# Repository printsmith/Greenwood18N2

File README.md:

# SP-110 Duo
Custom keyboard featuring a modified Southpaw 1800 layout with 2 nav clusters, LCD display and rotary encoders.

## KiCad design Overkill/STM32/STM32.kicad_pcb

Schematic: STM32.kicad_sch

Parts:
BT1: Battery_Cell; BatteryHolder_Keystone_1060_1x2032
C1, C15: 4.7u; C_0603_1608Metric_Pad1.08x0.95mm_HandSolder
C2, C3, C4, C5, C6, C7, C8, C9, C11, C12, C13, C14, C19, C20, C22, C23: 100n; C_0603_1608Metric_Pad1.08x0.95mm_HandSolder
C16, C17: 1u; C_0603_1608Metric_Pad1.08x0.95mm_HandSolder
C18, C24, C25, C26, C27, C28, C29, C30, C31, C32, C33: 100u; CP_EIA-6032-15_Kemet-U_Pad2.25x2.35mm_HandSolder
C21: 100nF; C_0603_1608Metric_Pad1.08x0.95mm_HandSolder
D1, D2, D3, D4, D5, D6, D7, D8, D9, D10, D11, D12, D13, D14, D15, D16, D17, D18, D19, D20, D21, D22, D23, D24, D25, D26, D27, D28, D29, D30, D31, D32, D33, D34, D35, D36, D37, D38, D39, D40, D41, D42, D43, D44, D45, D46, D47, D48, D49, D50, D51, D52, D53, D54, D55, D56, D57, D58, D59, D60, D61, D62, D63, D64, D65, D66, D67, D68, D69, D70, D71, D72, D73, D74, D75, D76, D77, D78, D79, D80, D81, D82, D83, D84, D85, D86, D87, D88, D89, D90, D91, D92, D93, D94, D95, D96, D97, D98, D99, D100, D101, D102, D103, D104, D105, D106, D107, D108, D109, D110, D111, D112, D113, D114, D115, D116, D117: D; D_SOD-123F
D118: SMF5.0CA; D_SOD-123F
D119, D120: 1N4148; D_SOD-123F
F1: 3.0A 1206 Polyfuse; Fuse_1206_3216Metric_Pad1.42x1.75mm_HandSolder
FB1: 4A/0805; Fuse_0805_2012Metric_Pad1.15x1.40mm_HandSolder
H1, H2, H3, H4, H5, H6, H7, H8, H9, H10: MountingHole; MountingHole_2.2mm_M2_DIN965_Pad
J1: USB_C_Receptacle_USB2.0; HRO-TYPE-C-31-M-12-HandSoldering-NoSBU
JP1: SolderJumper_2_Open; SolderJumper-2_P1.3mm_Open_TrianglePad1.0x1.5mm
LCD1: LCD-ST7789-2in
LED1, LED2, LED3, LED4, LED5, LED6, LED7, LED8, LED9, LED10, LED11, LED12, LED13, LED14, LED15, LED16, LED17, LED18, LED19, LED40, LED41, LED42, LED43, LED44, LED45, LED46, LED47, LED48, LED49, LED50, LED51, LED52, LED53, LED54, LED55, LED56, LED57, LED58, LED59, LED79, LED80, LED81, LED82, LED83, LED84, LED85, LED86, LED87, LED88, LED89, LED90, LED91, LED92, LED93, LED94, LED95, LED96, LED97: MX_SK6803MINI-E; LED_MX_6028R-ROT
LED20, LED21, LED22, LED23, LED24, LED25, LED26, LED27, LED28, LED29, LED30, LED31, LED32, LED33, LED34, LED35, LED36, LED37, LED38, LED39, LED60, LED61, LED62, LED63, LED64, LED65, LED66, LED67, LED68, LED69, LED70, LED71, LED72, LED73, LED74, LED75, LED76, LED77, LED78, LED98, LED99, LED100, LED101, LED102, LED103, LED104, LED105, LED106, LED107, LED108, LED109, LED110, LED111: MX_SK6803MINI-E; LED_MX_6028R
MX1, MX2, MX3, MX4, MX5, MX6, MX7, MX8, MX9, MX10, MX11, MX12, MX13, MX14, MX15, MX16, MX17, MX18, MX19, MX20, MX21, MX22, MX23, MX24, MX25, MX26, MX27, MX28, MX29, MX30, MX31, MX32, MX33, MX34, MX35, MX36, MX37, MX39, MX40, MX41, MX42, MX43, MX44, MX46, MX47, MX48, MX49, MX50, MX51, MX52, MX53, MX54, MX55, MX56, MX57, MX59, MX60, MX61, MX62, MX63, MX64, MX66, MX67, MX68, MX69, MX70, MX71, MX72, MX73, MX74, MX75, MX76, MX78, MX79, MX81, MX82, MX83, MX85, MX86, MX87, MX88, MX89, MX90, MX91, MX92, MX93, MX94, MX96, MX97, MX98, MX99, MX109, MX110, MX111: MX_SW_HS; SW_MX_HS_1u
MX38, MX100: MX_SW_HS; SW_MX_HS_2u
MX45, MX58, MX107, MX108: MX_SW_HS; SW_MX_HS_1.5u
MX65, MX95: MX_SW_HS; SW_MX_HS_1.75u
MX77, MX84, MX106: MX_SW_HS; SW_MX_HS_2.25u
MX80: MX_SW_HS; SW_MX_HS_2u_Vertical
MX101, MX102, MX103, MX105: MX_SW_HS; SW_MX_HS_1.25u
MX104: MX_SW_HS; SW_MX_HS_2.75u
Q1, Q2: AO3401A; SOT-23-3
Q3: MMUN2133LT1G; SOT-23-3
Q4, Q6: 2N7002; SOT-23-3
Q7: AO3401A; SOT-23
Q8: MMUN2233LT1G; SOT-23-3
R1: 120; R_0603_1608Metric_Pad0.98x0.95mm_HandSolder
R2, R3, R9, R15, R17, R20, R21, R22, R23, R24, R25: 68k; R_0603_1608Metric_Pad0.98x0.95mm_HandSolder
R4, R5, R6, R7, R8, R10, R11, R12, R13, R14, R16, R18, R19, R26, R27: 9.1k; R_0603_1608Metric_Pad0.98x0.95mm_HandSolder
R28: 9.1k; R_0805_2012Metric
RESET1: DFU; SW_SPST_SKQG_WithStem
SW1: RKJXT1F42001; Mouser Part Number 688-RKJXT1F42001
SW2: RotaryEncoder_Switch; RotaryEncoder_Alps_EC11E-Switch_Vertical_H20mm_Centred
TP1: VBUS; TestPoint
TP2: 5V; TestPoint
TP3: 3V3; TestPoint
TP4: GND; TestPoint
TP5: RST; TestPoint
TP6: SWC; TestPoint
TP7: SWD; TestPoint
U1: AZC199-04S; SOT-23-6
U2: W25Q32JVSSIQ; SOIC-8_5.23x5.23mm_P1.27mm
U3: LMV321; SOT-23-5
U4: MB85RS64; SOIC-8_3.9x4.9mm_P1.27mm
U5: AZ1117H-3.3TRE1; SOT-23-3
U6: STM32G474RETx; LQFP-64_10x10mm_P0.5mm
U7, U8: TPS2553DBVR-1; SOT-23-6_Handsoldering

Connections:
+3V3: C1.1, C2.1, C3.1, C4.1, C5.1, C6.1, C7.1, C11.1, C12.1, C17.2, JP1.1 (A), Q3.2 (E), R7.2, R10.2, R12.2, R14.2, TP3.1, U2.8 (VCC), U4.3 (~W), U4.7 (~HOLD), U4.8 (VCC), U5.2 (VO), U6.16 (VDD), U6.28 (VREF+), U6.29 (VDDA), U6.32 (VDD), U6.48 (VDD), U6.64 (VDD)
+5V: TP2.1
/VBUS_BLOCKED: Q1.2 (S), Q2.3 (D), R9.1, U1.5 (VBUS), U3.3 (-)
/VBUS_FERRITE: F1.2, FB1.1
/VBUS_FUSED: D118.1 (A1), F1.1, Q1.3 (D)
BOARD_NFAULT: R4.2, U6.30 (PB10), U7.4 (~FAULT)
BOOT0: C13.2, C14.2, R1.2, R2.2, U6.61 (PB8)
BOOT0_CHRG: D119.2 (A), Q3.1 (B), U6.60 (PB7)
CC1: J1.B5 (CC2), U1.3 (I/O4), U6.43 (PA9), U6.59 (PB6)
CC2: J1.A5 (CC1), U1.1 (I/O1), U6.44 (PA10), U6.57 (PB4)
COL3: MX6.1, MX7.1, MX26.1, MX27.1, MX46.1, MX47.1, MX66.1, MX67.1, MX85.1, MX102.1, MX103.1, U6.41 (PC9)
COL4: MX8.1, MX9.1, MX28.1, MX29.1, MX48.1, MX49.1, MX68.1, MX69.1, MX86.1, MX87.1, MX104.1, U6.40 (PC8)
COL5: MX10.1, MX11.1, MX30.1, MX31.1, MX50.1, MX51.1, MX70.1, MX71.1, MX88.1, MX89.1, MX105.1, U6.39 (PC7)
COL6: MX12.1, MX13.1, MX32.1, MX33.1, MX52.1, MX53.1, MX72.1, MX73.1, MX90.1, MX91.1, MX106.1, U6.38 (PC6)
COL7: MX14.1, MX15.1, MX34.1, MX35.1, MX54.1, MX55.1, MX74.1, MX75.1, MX92.1, MX93.1, MX107.1, U6.37 (PB15)
COL8: MX16.1, MX17.1, MX36.1, MX37.1, MX56.1, MX57.1, MX76.1, MX94.1, MX95.1, MX108.1, MX109.1, U6.36 (PB14)
COL9: MX18.1, MX19.1, MX38.1, MX39.1, MX58.1, MX59.1, MX77.1, MX78.1, MX96.1, MX97.1, MX110.1, MX111.1, U6.35 (PB13)
COL10: SW1.7 (COM)
CURR_1500mA_OK: Q4.1 (G), R26.1, U6.25 (PB1)
CURR_3000mA_OK: Q6.1 (G), R27.1, U6.24 (PB0)
CURR_LIM: R20.1, R23.1, R24.1, R25.1, U8.5 (ILIM)
D+: J1.A6 (D+), J1.B6 (D+), U1.6 (I/O2), U6.46 (PA12)
D-: J1.A7 (D-), J1.B7 (D-), U1.4 (I/O3), U6.45 (PA11)
EEP_CS: U4.1 (~S), U6.58 (PB5)
ENC1: D112.2 (A), SW2.S2
ENC1_A: C19.2, R8.1
ENC1_B: C20.2, R11.2
ENC2_A: C21.2, R13.1, U6.21 (PA7)
ENC2_B: C22.2, R16.2, U6.22 (PC4)
FLASH_CS: U2.1 (~CS), U6.42 (PA8)
LCD_BL_PWM: LCD1.8, U6.2 (PC13)
LCD_CS: LCD1.7, U6.62 (PB9)
LCD_DC: LCD1.6, U6.56 (PB3)
LCD_RST: LCD1.5, U6.55 (PD2)
LED_EN: R19.1, U6.33 (PB11), U8.3 (EN)
LED_MTRX_IN: LED4.3 (DIN), R28.2, U6.23 (PC5)
LED_NFAULT: R18.2, U6.26 (PB2), U8.4 (~FAULT)
LED_PWR: C24.1, C25.1, C26.1, C27.1, C28.1, C29.1, C30.1, C31.1, C32.1, C33.1, LED1.1 (VDD), LED2.1 (VDD), LED3.1 (VDD), LED4.1 (VDD), LED5.1 (VDD), LED6.1 (VDD), LED7.1 (VDD), LED8.1 (VDD), LED9.1 (VDD), LED10.1 (VDD), LED11.1 (VDD), LED12.1 (VDD), LED13.1 (VDD), LED14.1 (VDD), LED15.1 (VDD), LED16.1 (VDD), LED17.1 (VDD), LED18.1 (VDD), LED19.1 (VDD), LED20.1 (VDD), LED21.1 (VDD), LED22.1 (VDD), LED23.1 (VDD), LED24.1 (VDD), LED25.1 (VDD), LED26.1 (VDD), LED27.1 (VDD), LED28.1 (VDD), LED29.1 (VDD), LED30.1 (VDD), LED31.1 (VDD), LED32.1 (VDD), LED33.1 (VDD), LED34.1 (VDD), LED35.1 (VDD), LED36.1 (VDD), LED37.1 (VDD), LED38.1 (VDD), LED39.1 (VDD), LED40.1 (VDD), LED41.1 (VDD), LED42.1 (VDD), LED43.1 (VDD), LED44.1 (VDD), LED45.1 (VDD), LED46.1 (VDD), LED47.1 (VDD), LED48.1 (VDD), LED49.1 (VDD), LED50.1 (VDD), LED51.1 (VDD), LED52.1 (VDD), LED53.1 (VDD), LED54.1 (VDD), LED55.1 (VDD), LED56.1 (VDD), LED57.1 (VDD), LED58.1 (VDD), LED59.1 (VDD), LED60.1 (VDD), LED61.1 (VDD), LED62.1 (VDD), LED63.1 (VDD), LED64.1 (VDD), LED65.1 (VDD), LED66.1 (VDD), LED67.1 (VDD), LED68.1 (VDD), LED69.1 (VDD), LED70.1 (VDD), LED71.1 (VDD), LED72.1 (VDD), LED73.1 (VDD), LED74.1 (VDD), LED75.1 (VDD), LED76.1 (VDD), LED77.1 (VDD), LED78.1 (VDD), LED79.1 (VDD), LED80.1 (VDD), LED81.1 (VDD), LED82.1 (VDD), LED83.1 (VDD), LED84.1 (VDD), LED85.1 (VDD), LED86.1 (VDD), LED87.1 (VDD), LED88.1 (VDD), LED89.1 (VDD), LED90.1 (VDD), LED91.1 (VDD), LED92.1 (VDD), LED93.1 (VDD), LED94.1 (VDD), LED95.1 (VDD), LED96.1 (VDD), LED97.1 (VDD), LED98.1 (VDD), LED99.1 (VDD), LED100.1 (VDD), LED101.1 (VDD), LED102.1 (VDD), LED103.1 (VDD), LED104.1 (VDD), LED105.1 (VDD), LED106.1 (VDD), LED107.1 (VDD), LED108.1 (VDD), LED109.1 (VDD), LED110.1 (VDD), LED111.1 (VDD), R28.1, U8.6 (OUT)
MISO: U2.2 (DO(IO1)), U4.2 (Q), U6.53 (PC11)
MOSI: LCD1.4, U2.5 (DI(IO0)), U4.5 (D), U6.54 (PC12)
NRST: C9.2, D120.2 (A), U6.7 (PG10)
unnamed: D1.2 (A), MX1.2
unnamed: D2.1 (K), MX2.2
unnamed: D3.2 (A), MX3.2
unnamed: D4.1 (K), MX4.2
unnamed: D5.2 (A), MX5.2
unnamed: D6.1 (K), MX6.2
unnamed: D7.2 (A), MX7.2
unnamed: D8.1 (K), MX8.2
unnamed: D9.2 (A), MX9.2
unnamed: D10.1 (K), MX10.2
unnamed: D11.2 (A), MX11.2
unnamed: D12.1 (K), MX12.2
unnamed: D13.2 (A), MX13.2
unnamed: D14.1 (K), MX14.2
unnamed: D15.2 (A), MX15.2
unnamed: D16.1 (K), MX16.2
unnamed: D17.2 (A), MX17.2
unnamed: D18.1 (K), MX18.2
unnamed: D19.2 (A), MX19.2
unnamed: D20.1 (K), MX20.2
unnamed: D21.2 (A), MX21.2
unnamed: D22.1 (K), MX22.2
unnamed: D23.2 (A), MX23.2
unnamed: D24.1 (K), MX24.2
unnamed: D25.2 (A), MX25.2
unnamed: D26.1 (K), MX26.2
unnamed: D27.2 (A), MX27.2
unnamed: D28.1 (K), MX28.2
unnamed: D29.2 (A), MX29.2
unnamed: D30.1 (K), MX30.2
unnamed: D31.2 (A), MX31.2
unnamed: D32.1 (K), MX32.2
unnamed: D33.2 (A), MX33.2
unnamed: D34.1 (K), MX34.2
unnamed: D35.2 (A), MX35.2
unnamed: D36.1 (K), MX36.2
unnamed: D37.2 (A), MX37.2
unnamed: D38.1 (K), MX38.2
unnamed: D39.2 (A), MX39.2
unnamed: D40.1 (K), MX40.2
unnamed: D41.2 (A), MX41.2
unnamed: D42.1 (K), MX42.2
unnamed: D43.2 (A), MX43.2
unnamed: D44.1 (K), MX44.2
unnamed: D45.2 (A), MX45.2
unnamed: D46.1 (K), MX46.2
unnamed: D47.2 (A), MX47.2
unnamed: D48.1 (K), MX48.2
unnamed: D49.2 (A), MX49.2
unnamed: D50.1 (K), MX50.2
unnamed: D51.2 (A), MX51.2
unnamed: D52.1 (K), MX52.2
unnamed: D53.2 (A), MX53.2
unnamed: D54.1 (K), MX54.2
unnamed: D55.2 (A), MX55.2
unnamed: D56.1 (K), MX56.2
unnamed: D57.2 (A), MX57.2
unnamed: D58.1 (K), MX58.2
unnamed: D59.2 (A), MX59.2
unnamed: D60.1 (K), MX60.2
unnamed: D61.2 (A), MX61.2
unnamed: D62.1 (K), MX62.2
unnamed: D63.2 (A), MX63.2
unnamed: D64.1 (K), MX64.2
unnamed: D65.2 (A), MX65.2
unnamed: D66.1 (K), MX66.2
unnamed: D67.2 (A), MX67.2
unnamed: D68.1 (K), MX68.2
unnamed: D69.2 (A), MX69.2
unnamed: D70.1 (K), MX70.2
unnamed: D71.2 (A), MX71.2
unnamed: D72.1 (K), MX72.2
unnamed: D73.2 (A), MX73.2
unnamed: D74.1 (K), MX74.2
unnamed: D75.2 (A), MX75.2
unnamed: D76.1 (K), MX76.2
unnamed: D77.1 (K), MX77.2
unnamed: D78.2 (A), MX78.2
unnamed: D79.1 (K), MX79.2
unnamed: D81.1 (K), MX81.2
unnamed: D82.2 (A), MX82.2
unnamed: D83.1 (K), MX83.2
unnamed: D84.2 (A), MX84.2
unnamed: D85.2 (A), MX85.2
unnamed: D86.1 (K), MX86.2
unnamed: D87.2 (A), MX87.2
unnamed: D88.1 (K), MX88.2
unnamed: D89.2 (A), MX89.2
unnamed: D90.1 (K), MX90.2
unnamed: D91.2 (A), MX91.2
unnamed: D92.1 (K), MX92.2
unnamed: D93.2 (A), MX93.2
unnamed: D94.1 (K), MX94.2
unnamed: D95.2 (A), MX95.2
unnamed: D96.1 (K), MX96.2
unnamed: D97.2 (A), MX97.2
unnamed: D98.1 (K), MX98.2
unnamed: D99.1 (K), MX99.2
unnamed: D100.1 (K), MX100.2
unnamed: D101.2 (A), MX101.2
unnamed: D102.1 (K), MX102.2
unnamed: D103.2 (A), MX103.2
unnamed: D104.2 (A), MX104.2
unnamed: D105.2 (A), MX105.2
unnamed: D106.2 (A), MX106.2
unnamed: D107.2 (A), MX107.2
unnamed: D108.1 (K), MX108.2
unnamed: D109.2 (A), MX109.2
unnamed: D110.1 (K), MX110.2
unnamed: D111.2 (A), MX111.2
unnamed: D119.1 (K), D120.1 (K), RESET1.2
unnamed: LED1.3 (DIN), LED2.2 (DOUT)
unnamed: LED1.2 (DOUT), LED20.3 (DIN)
unnamed: LED2.3 (DIN), LED3.2 (DOUT)
unnamed: LED3.3 (DIN), LED4.2 (DOUT)
unnamed: LED5.3 (DIN), LED6.2 (DOUT)
unnamed: LED6.3 (DIN), LED7.2 (DOUT)
unnamed: LED7.3 (DIN), LED8.2 (DOUT)
unnamed: LED8.3 (DIN), LED9.2 (DOUT)
unnamed: LED10.3 (DIN), LED11.2 (DOUT)
unnamed: LED9.3 (DIN), LED10.2 (DOUT)
unnamed: LED11.3 (DIN), LED12.2 (DOUT)
unnamed: LED12.3 (DIN), LED13.2 (DOUT)
unnamed: LED13.3 (DIN), LED14.2 (DOUT)
unnamed: LED14.3 (DIN), LED15.2 (DOUT)
unnamed: LED15.3 (DIN), LED16.2 (DOUT)
unnamed: LED16.3 (DIN), LED17.2 (DOUT)
unnamed: LED17.3 (DIN), LED18.2 (DOUT)
unnamed: LED18.3 (DIN), LED19.2 (DOUT)
unnamed: LED19.3 (DIN), LED39.2 (DOUT)
unnamed: LED20.2 (DOUT), LED21.3 (DIN)
unnamed: LED21.2 (DOUT), LED22.3 (DIN)
unnamed: LED22.2 (DOUT), LED23.3 (DIN)
unnamed: LED23.2 (DOUT), LED24.3 (DIN)
unnamed: LED24.2 (DOUT), LED44.3 (DIN)
unnamed: LED25.3 (DIN), LED45.2 (DOUT)
unnamed: LED25.2 (DOUT), LED26.3 (DIN)
unnamed: LED26.2 (DOUT), LED27.3 (DIN)
unnamed: LED27.2 (DOUT), LED28.3 (DIN)
unnamed: LED28.2 (DOUT), LED29.3 (DIN)
unnamed: LED29.2 (DOUT), LED30.3 (DIN)
unnamed: LED30.2 (DOUT), LED31.3 (DIN)
unnamed: LED31.2 (DOUT), LED32.3 (DIN)
unnamed: LED32.2 (DOUT), LED33.3 (DIN)
unnamed: LED33.2 (DOUT), LED34.3 (DIN)
unnamed: LED34.2 (DOUT), LED35.3 (DIN)
unnamed: LED35.2 (DOUT), LED36.3 (DIN)
unnamed: LED36.2 (DOUT), LED37.3 (DIN)
unnamed: LED37.2 (DOUT), LED38.3 (DIN)
unnamed: LED38.2 (DOUT), LED39.3 (DIN)
unnamed: LED40.3 (DIN), LED41.2 (DOUT)
unnamed: LED40.2 (DOUT), LED60.3 (DIN)
unnamed: LED41.3 (DIN), LED42.2 (DOUT)
unnamed: LED42.3 (DIN), LED43.2 (DOUT)
unnamed: LED43.3 (DIN), LED44.2 (DOUT)
unnamed: LED45.3 (DIN), LED46.2 (DOUT)
unnamed: LED46.3 (DIN), LED47.2 (DOUT)
unnamed: LED47.3 (DIN), LED48.2 (DOUT)
unnamed: LED48.3 (DIN), LED49.2 (DOUT)
unnamed: LED49.3 (DIN), LED50.2 (DOUT)
unnamed: LED50.3 (DIN), LED51.2 (DOUT)
unnamed: LED51.3 (DIN), LED52.2 (DOUT)
unnamed: LED52.3 (DIN), LED53.2 (DOUT)
unnamed: LED53.3 (DIN), LED54.2 (DOUT)
unnamed: LED54.3 (DIN), LED55.2 (DOUT)
unnamed: LED55.3 (DIN), LED56.2 (DOUT)
unnamed: LED56.3 (DIN), LED57.2 (DOUT)
unnamed: LED57.3 (DIN), LED58.2 (DOUT)
unnamed: LED58.3 (DIN), LED59.2 (DOUT)
unnamed: LED59.3 (DIN), LED78.2 (DOUT)
unnamed: LED60.2 (DOUT), LED61.3 (DIN)
unnamed: LED61.2 (DOUT), LED62.3 (DIN)
unnamed: LED62.2 (DOUT), LED63.3 (DIN)
unnamed: LED63.2 (DOUT), LED64.3 (DIN)
unnamed: LED64.2 (DOUT), LED83.3 (DIN)
unnamed: LED65.3 (DIN), LED84.2 (DOUT)
unnamed: LED65.2 (DOUT), LED66.3 (DIN)
unnamed: LED66.2 (DOUT), LED67.3 (DIN)
unnamed: LED67.2 (DOUT), LED68.3 (DIN)
unnamed: LED68.2 (DOUT), LED69.3 (DIN)
unnamed: LED69.2 (DOUT), LED70.3 (DIN)
unnamed: LED70.2 (DOUT), LED71.3 (DIN)
unnamed: LED71.2 (DOUT), LED72.3 (DIN)
unnamed: LED72.2 (DOUT), LED73.3 (DIN)
unnamed: LED73.2 (DOUT), LED74.3 (DIN)
unnamed: LED74.2 (DOUT), LED75.3 (DIN)
unnamed: LED75.2 (DOUT), LED76.3 (DIN)
unnamed: LED76.2 (DOUT), LED77.3 (DIN)
unnamed: LED77.2 (DOUT), LED78.3 (DIN)
unnamed: LED79.3 (DIN), LED80.2 (DOUT)
unnamed: LED79.2 (DOUT), LED98.3 (DIN)
unnamed: LED80.3 (DIN), LED81.2 (DOUT)
unnamed: LED81.3 (DIN), LED82.2 (DOUT)
unnamed: LED82.3 (DIN), LED83.2 (DOUT)
unnamed: LED84.3 (DIN), LED85.2 (DOUT)
unnamed: LED85.3 (DIN), LED86.2 (DOUT)
unnamed: LED86.3 (DIN), LED87.2 (DOUT)
unnamed: LED87.3 (DIN), LED88.2 (DOUT)
unnamed: LED88.3 (DIN), LED89.2 (DOUT)
unnamed: LED89.3 (DIN), LED90.2 (DOUT)
unnamed: LED90.3 (DIN), LED91.2 (DOUT)
unnamed: LED91.3 (DIN), LED92.2 (DOUT)
unnamed: LED92.3 (DIN), LED93.2 (DOUT)
unnamed: LED93.3 (DIN), LED94.2 (DOUT)
unnamed: LED94.3 (DIN), LED95.2 (DOUT)
unnamed: LED95.3 (DIN), LED97.2 (DOUT)
unnamed: LED96.2 (DOUT), LED97.3 (DIN)
unnamed: LED98.2 (DOUT), LED99.3 (DIN)
unnamed: LED99.2 (DOUT), LED100.3 (DIN)
unnamed: LED100.2 (DOUT), LED101.3 (DIN)
unnamed: LED101.2 (DOUT), LED102.3 (DIN)
unnamed: LED102.2 (DOUT), LED103.3 (DIN)
unnamed: LED103.2 (DOUT), LED104.3 (DIN)
unnamed: LED104.2 (DOUT), LED105.3 (DIN)
unnamed: LED105.2 (DOUT), LED106.3 (DIN)
unnamed: LED106.2 (DOUT), LED107.3 (DIN)
unnamed: LED107.2 (DOUT), LED108.3 (DIN)
unnamed: LED108.2 (DOUT), LED109.3 (DIN)
unnamed: LED109.2 (DOUT), LED110.3 (DIN)
unnamed: LED110.2 (DOUT), LED111.3 (DIN)
unnamed: LED96.3 (DIN), LED111.2 (DOUT)
unnamed: Q2.1 (G), U3.4
unnamed: Q3.3 (C), R1.1
unnamed: Q4.3 (D), R23.2
unnamed: Q6.3 (D), R24.2, R25.2
unnamed: R2.1, R3.1
unnamed: R5.2, R6.1
unnamed: R15.2, R17.1
unnamed: R20.2, R21.2
unnamed: R21.1, R22.1
unnamed: R5.1, U7.5 (ILIM)
PLUG_DETECT: R9.2, R15.1, U6.34 (PB12)
RESET: TP5.1
RKJ-A: D116.2 (A), SW1.1 (A)
RKJ-B: D114.2 (A), SW1.4 (B)
RKJ-C: D113.2 (A), SW1.6 (C)
RKJ-D: D117.2 (A), SW1.9 (D_1)
RKJ-P: D115.2 (A), SW1.2 (PUSH)
ROT1_A: R7.1, R8.2, SW1.10 (ENCODER_A)
ROT1_B: R10.1, R11.1, SW1.5 (ENCODER_B)
ROT2_A: R12.1, R13.2, SW2.A
ROT2_B: R14.1, R16.1, SW2.B
ROW1: D20.2 (A), D21.1 (K), D22.2 (A), D23.1 (K), D24.2 (A), D25.1 (K), D26.2 (A), D27.1 (K), D28.2 (A), D29.1 (K), D30.2 (A), D31.1 (K), D32.2 (A), D33.1 (K), D34.2 (A), D35.1 (K), D36.2 (A), D37.1 (K), D38.2 (A), D39.1 (K), D113.1 (K)
ROW2: D40.2 (A), D41.1 (K), D42.2 (A), D43.1 (K), D44.2 (A), D45.1 (K), D46.2 (A), D47.1 (K), D48.2 (A), D49.1 (K), D50.2 (A), D51.1 (K), D52.2 (A), D53.1 (K), D54.2 (A), D55.1 (K), D56.2 (A), D57.1 (K), D58.2 (A), D59.1 (K), D114.1 (K)
ROW3: D60.2 (A), D61.1 (K), D62.2 (A), D63.1 (K), D64.2 (A), D65.1 (K), D66.2 (A), D67.1 (K), D68.2 (A), D69.1 (K), D70.2 (A), D71.1 (K), D72.2 (A), D73.1 (K), D74.2 (A), D75.1 (K), D76.2 (A), D77.2 (A), D78.1 (K), D115.1 (K)
ROW4: D79.2 (A), D81.2 (A), D82.1 (K), D83.2 (A), D84.1 (K), D85.1 (K), D86.2 (A), D87.1 (K), D88.2 (A), D89.1 (K), D90.2 (A), D91.1 (K), D92.2 (A), D93.1 (K), D94.2 (A), D95.1 (K), D96.2 (A), D97.1 (K), D116.1 (K)
ROW5: D80.1 (K), D80.2 (A), D98.2 (A), D99.2 (A), D100.2 (A), D101.1 (K), D102.2 (A), D103.1 (K), D104.1 (K), D105.1 (K), D106.1 (K), D107.1 (K), D108.2 (A), D109.1 (K), D110.2 (A), D111.1 (K), D117.1 (K), MX80.2
SCK: LCD1.3, U2.6 (CLK), U4.6 (C), U6.52 (PC10)
SHIELD: J1.S1 (SHIELD)
SWC: TP6.1
SWCLK: U6.50 (PA14)
SWD: TP7.1
SWDIO: U6.49 (PA13)
VBAT: BT1.1 (+), C8.1, JP1.2 (B), U6.1 (VBAT)
VBUS: C15.1, Q2.2 (S), R4.1, TP1.1, U3.1 (+), U3.5 (V+), U7.1 (IN), U7.3 (EN)
V_USB: FB1.2, J1.A4 (VBUS), J1.A9 (VBUS), J1.B4 (VBUS), J1.B9 (VBUS)

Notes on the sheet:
TEST POINTS
Encoders
Transient voltage suppression
Output
MCU
LCD Power
SPI FLASH
"Smart" -- requires USBPD running on MCU. Djinn code currently supports it -- DBCC pins will allow usage on macOS until CC pins are configured
SK6803 Pull-up
NOTE: MCU power layout considerations: - Require MCU-local power "peninsula" - 4.7uF between the local 3V3+GND peninsula and rest of board. - Single 3V3 input to 4.7uF, star pattern where possible. - One capacitor per power pin, decoupled to local GND.
Reverse current blocking -- ideal diode configuration
USB Input
Reset Circuit
USB CC Lines
NOTE: Dynamically changes current limiter Rset: Resistor series/parallel networks selected to minimise unique BOM entries When USB=500mA, select Rset = 204k = 201k9 @ 1% = 156mA/side When USB=1500mA, select Rset = 204k||68k = 50k5 @ 1% = 576mA/side When USB=3000mA, select Rset = 204k||68k||34k = 20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
Display
NOTE: BOARD_NFAULT needs to be connected to a 5V-tolerant pin on the MCU
SK6803 Current Limiter
SPI EEPROM
NOTE: 68k||68k =34k
LED Matrix
M2 Mounting Holes
Polarity protection
Switch Matrix
NOTE: BOOT0: L=0.99V, H=2.31V nRST: L=0.99V, H=2.31V RC network value designed to ensure that at time of sampling: nRST=2.31V=H, BOOT0=2.75V=H
Board 5V current limiter
NOTE: 68k+68k+68k =204k
Data line ESD protection
Current limiting
NOTE: Resistor divider to determine if plug is present. - GPIO is input, with no pull-down resistor active - 68k/136k divider -> 5V -> 3.33V
3.3V Regulator
NOTE: - Plug detect connected to ADC - 3.33V nominal at 5V - ADC reads can detect droop
NOTE: 2x 9k1 = 18.2k @ 1% = 18k0 low, 18k4 high Current limit range between 1310mA and 1517mA
Plug detection
NOTE: Place each 100uF capacitor at each row branch point

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
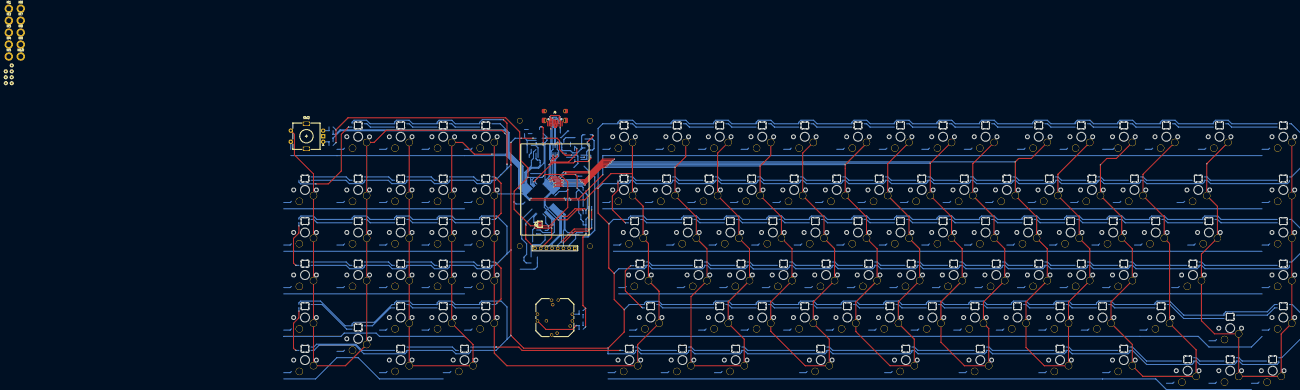
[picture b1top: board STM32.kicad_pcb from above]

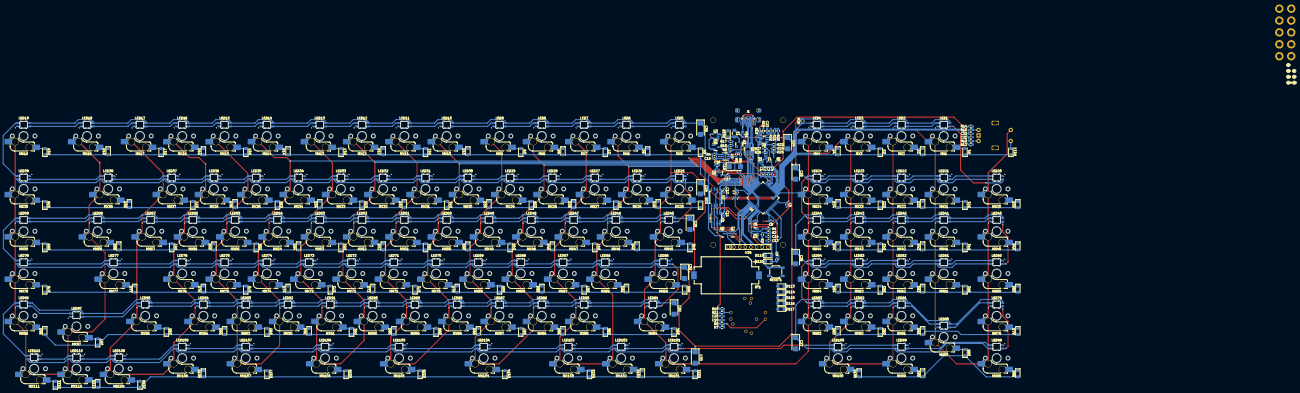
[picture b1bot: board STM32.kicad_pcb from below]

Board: 2 copper layers, 443 parts (421 on the bottom side), 298 nets.

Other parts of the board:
Q5: AO3401A; SOT-23

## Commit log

2023-11-25 Initial commit of KiCAD project
2023-11-25 Add .pretty for KiCAD
    - _mod files added
    - 3D models added
    - update keyboard name in schematics to match
2023-11-27 Current Limiter update
    add in an RC delay circuit for the EN pin of the TPS2553 current limiter. This should allow the USB to handshake and configure itself and the allow the current limiter to then start working.
2023-11-27 Rework of encoders
    Remove the dual LED, switch and encoder footprints, it was too complex and I want encoders, I will never be using them as just mx switches.
    Changed the encoder under the LCD to an EVQWGD001 since it wont block the screen and be easier to use with just your index finger.
2023-11-28 Add reset switch
2023-11-28 Rename
2023-11-28 Add .lck files to gitignore
2023-11-28 Update name
2023-12-18 change name
2024-01-11 Revert "update"
    This reverts commit 5ff72173e5904ec7ac0860fae9239c8bb0f8e9f6.
2024-01-12 Update diode directions
    Correct diode direction so that columns are not reversed in software.
2024-01-15 Fix crossed pins for display
    Update so that SPI pins are in correct place
2024-01-26 Merge RGB EN and LCD VCC
    Now RGB EN pin controls both RGB and LCD. This is due to lack of GPIO and a want to turn off the LCD when the keyboard goes to sleep.
2024-01-26 Change LCD power to LED power signal
2024-01-26 Add RC delay for LED current limiter
    Changing the GPIO for LED enable to only enable the LCD screen. Switching the current limiter enable to an RC delay circuit.
2024-01-26 update footprints
2024-01-30 Modify diode footprint, add LCD PWR circuit
2024-01-31 Update decoupling
2024-02-01 add footprints for LCDs
    add autosave to gitignore
2024-02-07 PCB rev01 update
2024-02-07 Align schematic to PCB
2024-02-08 update LED pwr tracks
2024-02-10 Route SMD components
2024-02-10 add gnd vias
2024-02-12 update traces
2024-02-13 update reset pin trace
2024-02-13 Overhaul File structure
2024-02-17 RP2040 based rev2
    Add integrated MCU to board, RP2040 with all supporting hardware
2024-02-17 schematic layout update
2024-02-18 update dev board circuit
2024-02-19 update rp2040 version
2024-02-24 Massive update
    Joystick encoder added to next version to replace encoder 2 above left nav cluster
2024-02-24 save
2024-06-13 update repo organization
2024-06-17 Update matrix/leds
    switch library footprints and seperate matrix sw and leds in diagram
2024-06-19 update for rjk
2024-06-24 update new design
2024-06-28 check ing
2024-06-28 STM32
2024-07-06 daily
2024-11-08 update layout & pins
2024-11-27 Update PCB traces
2024-11-28 Rotate mcu & wire nets
